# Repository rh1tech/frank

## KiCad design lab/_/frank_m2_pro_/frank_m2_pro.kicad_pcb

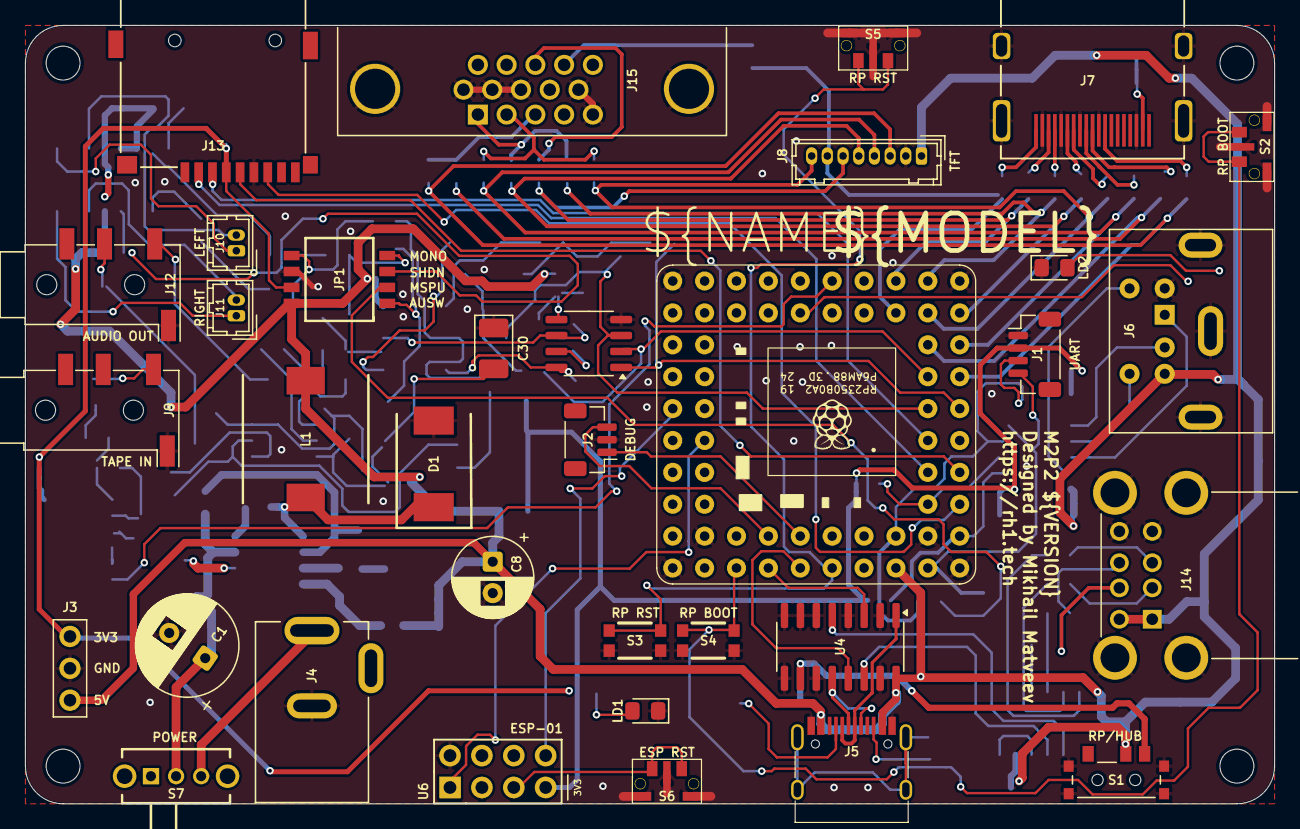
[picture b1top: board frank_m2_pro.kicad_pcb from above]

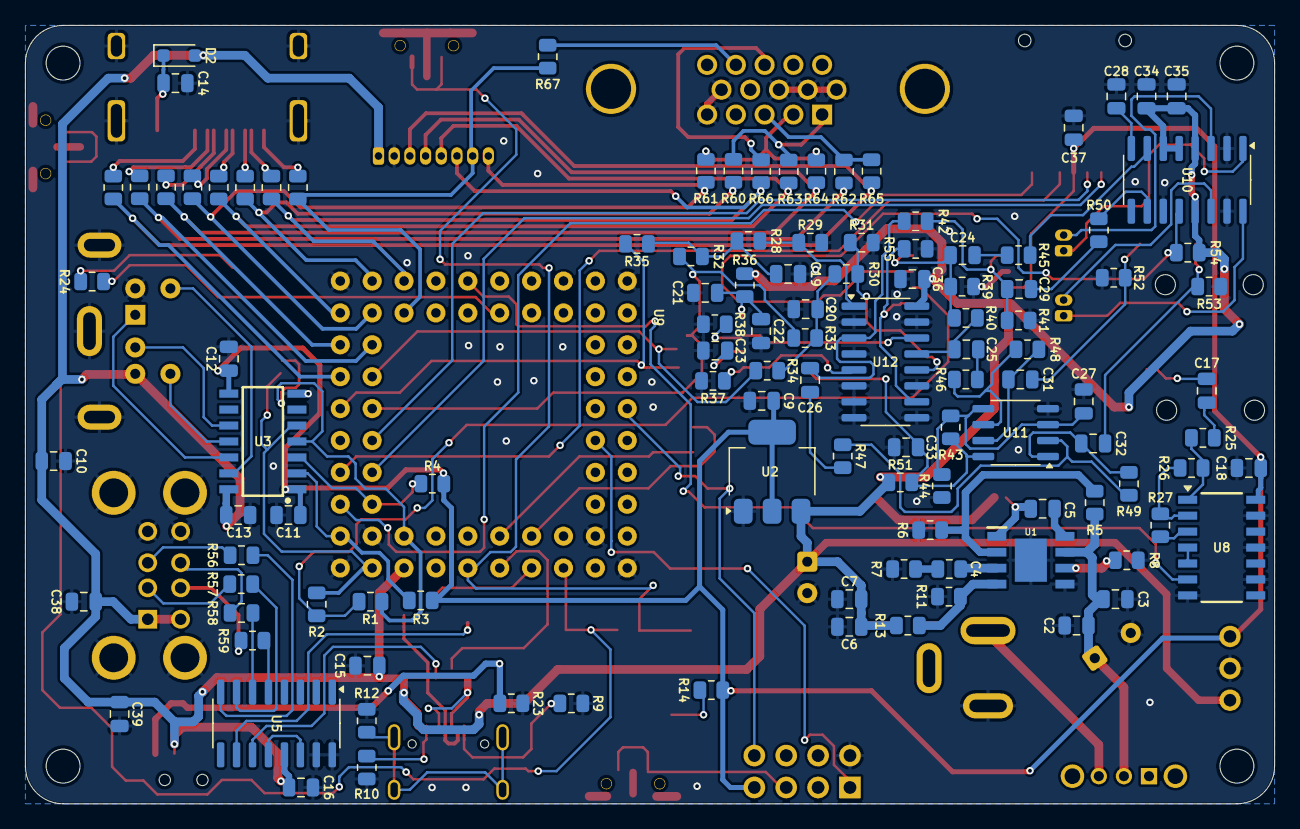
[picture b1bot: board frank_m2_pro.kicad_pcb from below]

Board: 2 copper layers, 99.5 x 62.0 mm, 150 parts (112 on the bottom side), 119 nets.

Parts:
C1: 680u; Capacitor (Radial_D8.0mm_P3.50mm)
C2, C7, C9, C21, C23, C25, C26, C27, C31, C32, C38, C39: 10u; C_0805_2012Metric
C3, C5, C6, C10, C11, C12, C13, C14, C15, C17, C18, C22, C28, C33, C36, C37: 100n; C_0805_2012Metric
C4: 150pF; R_0805_2012Metric
C8: 220u; Capacitor (Radial_D6.3mm_P2.50mm)
C16: 4.7u; C_0805_2012Metric
C19, C20: 47n; C_0805_2012Metric
C24, C29, C34: 1u; C_0805_2012Metric
C30: 10u; Capacitor (3528, tantalum, polar)
C35: 47u; C_0805_2012Metric
D1: 1N5822; SS34
D2: 1N5819WS; Diode (SOD-323)
H1, H2, H3, H4: Hole 2.7mm; Mounting Hole (2.7mm)
J1: UART; JST_SH_BM04B-SRSS-TB_1x04-1MP_P1.00mm_Vertical
J2: DEBUG; JST_SH_BM03B-SRSS-TB_1x03-1MP_P1.00mm_Vertical
J3: PWR; Pin Header (1x03)
J4: DC-005-5A-2.0; XKB_DC-005-5A-2.0
J5: USB4215-03-A; USB Type C
J6: MDC-036; MiniDIN (6 Pin, female)
J7: DC3RX19JA2; HDMI (female)
J8: Pin Header 1x08; Connector Female 1.25 JST 8P
J9, J12: PJ-320D; Jack (3.5mm, PJ-320D)
J10: PAM L; Connector Female 1.25 JST 2P
J11: PAM R; Connector Female 1.25 JST 2P
J13: 104031-0811; MicroSD (SMD, long)
J14: SS-52100-004; USB Type A (stacked)
J15: VGA; D-SUB (15 pin, female)
JP1: Config Switches; CHS04TB1
L1: 22uH; CDRH104RNP
LD1: Green; LED (0805)
LD2: Blue; LED (0805)
R1, R2, R3, R4, R23, R28, R30, R40, R42, R43, R44, R45, R46, R47, R50, R54, R55: 10K; R_0805_2012Metric
R5, R7, R8, R26, R27: 100K; R_0805_2012Metric
R6: 24K; R_0805_2012Metric
R9, R10: 5.1K; R_0805_2012Metric
R11: 8.2K; R_0805_2012Metric
R12: 1M; R_0805_2012Metric
R13: 43K; R_0805_2012Metric
R14, R24, R34, R35, R63, R64, R65: 1K; R_0805_2012Metric
R15, R16, R17, R18, R19, R20, R21, R22: 270R; R_0805_2012Metric
R25: 4.7K; R_0805_2012Metric
R29, R31, R32, R33, R39, R41: 2K; R_0805_2012Metric
R36, R51, R66, R67: 100R; R_0805_2012Metric
R37, R38: 470R; R_0805_2012Metric
R48, R49: 47K; R_0805_2012Metric
R52, R53: 20K; R_0805_2012Metric
R56, R57, R58, R59: 22R; R_0805_2012Metric
R60, R61, R62: 330R; R_0805_2012Metric
S1: MSK12C02; SW_MSK12C02
S2: RP BOOT; TS-1234VW
S3: RP Reset; KMR_2
S4: RP BOOT; KMR_2
S5: RP Reset; TS-1234VW
S6: ESP Reset; TS-1234VW
S7: SK12D07VG3NS
U1: MP1584EN-LF-Z; SOIC127P600X170-9N
U2: AMS1117 3.3; SOT-223
U3: TXS0104EDR; SOIC127P600X175-14N
U4, U12: 74HC4052D; SOP-16
U5: MW7211A; SOP-16
U6: ESP-01v090; ESP-01
U7: Pimoroni PGA2350; PGA2350
U8: CD4069UBM; SOIC127P600X175-14N
U9: TDA1387T; SO-8
U10: PAM8403D; SOP-16
U11: LM358; SO-8

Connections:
+3V3: C9.1, C11.1, C12.1, C18.1, C37.2, J1.2, J3.1, J13.4 (VDD), JP1.7, R3.2, R4.2, R14.2, U2.2 (VO), U3.1 (VCCA), U3.8 (OE), U6.7 (VCC), U8.14 (VDD)
/AMP_L: C25.1, R40.1, U12.13 (1Z)
/AMP_OUT_L: C31.2, J12.T, R52.2
/AMP_OUT_R: C32.2, J12.R, R53.2
/AMP_R: C26.1, R42.1, U12.3 (2Z)
/AUDIOSW: JP1.1, R55.2, U12.10 (S0)
/Audio/AMP_PAM_OUTL_M: J10.2, U10.3 (-OUTL)
/Audio/AMP_PAM_OUTL_P: J10.1, U10.1 (+OUT_L)
/Audio/AMP_PAM_OUTR_M: J11.2, U10.14 (-OUT_R)
/Audio/AMP_PAM_OUTR_P: J11.1, U10.16 (+OUT_R)
/BOOTSEL: S2.1, S4.1, S4.3, U7.51 (BOOTSEL)
/ERST: S6.1, U6.5 (RST)
/HDM: U4.5 (2Y1), U5.10 (DMU)
/HDP: U4.14 (1Y1), U5.11 (DPU)
/MONO_L: C24.1, JP1.4, R39.1, R40.2
/MONO_R: C29.1, JP1.5, R41.1, R42.2
/MSPUP3V3: JP1.2, R1.2, R2.2
/PDM: U4.3 (2Z), U7.53 (USB_DM)
/PDP: U4.13 (1Z), U7.54 (USB_DP)
/PGPIO0: J1.3, R1.1, U3.4 (A3), U7.61 (GP0)
/PGPIO1: J1.4, R2.1, U3.5 (A4), U7.62 (GP1)
/PGPIO2: R3.1, U3.2 (A1), U7.2 (GP2)
/PGPIO3: R4.1, U3.3 (A2), U7.3 (GP3)
/PGPIO4: J13.7 (DAT0), U7.4 (GP4)
/PGPIO5: J13.2 (DAT3/CD), U7.5 (GP5)
/PGPIO6: J13.5 (CLK), U7.6 (GP6)
/PGPIO7: J13.3 (CMD), U7.7 (GP7)
/PGPIO9: R32.1, R33.1, U7.9 (GP9), U9.3 (DATA)
/PGPIO10: R35.2, U7.10 (GP10), U9.1 (SCLK)
/PGPIO11: R34.2, U7.11 (GP11), U9.2 (LRCK)
/PGPIO12: J8.3, R17.2, R65.1, U7.12 (GP12)
/PGPIO13: R21.2, R62.1, U7.13 (GP13)
/PGPIO14: J8.4, R15.2, R64.1, U7.14 (GP14)
/PGPIO15: J8.8, R18.2, R61.1, U7.15 (GP15)
/PGPIO16: J8.5, R19.2, R63.1, U7.16 (GP16)
/PGPIO17: R22.2, R60.1, U7.17 (GP17)
/PGPIO18: J8.6, R16.2, R66.2, U7.19 (GP18)
/PGPIO19: J8.7, R20.2, R67.2, U7.20 (GP19)
/PGPIO22: U7.23 (GP22), U8.6 (I=*C)
/PGPIO38: U6.8 (URXD), U7.40 (GP38)
/PGPIO39: U6.1 (UTXD), U7.41 (GP39)
/PRUN: S3.1, S3.3, S5.1, U7.56 (RUN)
/PS2/KB_CLK_5V: J6.5, U3.13 (B1)
/PS2/KB_DATA_5V: J6.1, U3.12 (B2)
/PS2/MS_CLK_5V: J6.6, U3.11 (B3)
/PS2/MS_DATA_5V: J6.2, U3.10 (B4)
/PSWCLK: J2.1, U7.55 (SWCLK)
/PSWDIO: J2.3, U7.52 (SWDIO)
/PWM_L: R30.2, R31.1, U12.12 (1Y0)
/PWM_R: R28.2, R29.1, U12.1 (2Y0)
/Power/VBUS_IN: C1.1, C2.1, C3.1, R5.2, S7.2, U1.7 (VIN)
/SD1M: R57.1, U5.7 (DM3)
/SD1P: R56.1, U5.8 (DP3)
/SD2M: R59.1, U5.5 (DM2)
/SD2P: R58.1, U5.6 (DP2)
/SHND: JP1.3, R54.2, U10.12 (SHND)
/TDA_L: R38.2, U9.6 (A_LEFT), U12.14 (1Y1)
/TDA_R: R37.1, U9.8 (A_RIGHT), U12.5 (2Y1)
/Tape In/TAPE: C17.2, J9.T
/UDM: J5.5 (DN2), J5.7 (DN1), U4.1 (2Y0)
/UDP: J5.6 (DP1), J5.8 (DP2), U4.12 (1Y0)
/USBSW: R23.2, S1.3, U4.10 (S0)
GND: C1.2, C2.2, C3.2, C6.1, C7.2, C8.2, C9.2, C10.2, C11.2, C12.2, C13.2, C14.2, C15.1, C16.2, C18.2, C19.2, C20.2, C21.2, C22.2, C23.2, C27.1, C28.2, C30.1, C33.1, C34.2, C35.2, C36.1, C37.1, C38.2, C39.2, D1.2 (A), J1.1, J2.2, J3.2, J4.2, J5.1 (GND), J5.12 (GND), J6.3, J7.2 (G_D2), J7.5 (G_D1), J7.8 (G_D0), J7.11 (G_CLK), J7.17 (G_DDC/CEC), J7.20 (SHIELD1), J7.21 (SHIELD2), J7.22 (SHIELD3), J7.23 (SHIELD4), J8.2, J9.S, J12.S, J13.6 (VSS), J14.4 (GND1), J14.8 (GND2), J14.9 (Shield), J15.0, J15.5, J15.6, J15.7, J15.8, J15.10, JP1.6, LD1.1 (K), LD2.1 (K), R6.2, R7.2, R8.2, R9.1, R10.1, R11.1, R12.1, R23.1, R29.2, R31.2, R37.2, R38.1, R39.2, R41.2, R44.1, R52.1, R53.1, R55.1, S1.4_1 (GND), S1.4_2 (GND), S1.4_3 (GND), S1.4_4 (GND), S2.2, S2.3 (GND), S3.2, S3.4, S4.2, S4.4, S5.2, S5.3 (GND), S6.2, S6.3 (GND), U1.5 (GND), U1.9 (EP), U2.1 (GND), U3.7 (GND), U4.2 (2Y2), U4.4 (2Y3), U4.6 (~E), U4.7 (VEE), U4.8 (GND), U4.9 (S1), U4.11 (1Y3), U4.15 (1Y2), U5.15 (GND), U5.16 (GND), U6.2 (GND), U7.1 (GND), U7.18 (GND), U7.33 (GND), U7.48 (GND), U8.7 (VSS), U8.9 (D14), U8.11 (E), U8.13 (F), U9.4 (AGND), U10.2 (PGND), U10.11 (GND), U10.15 (PGND), U11.4 (V-), U12.2 (2Y2), U12.4 (2Y3), U12.6 (~E), U12.7 (VEE), U12.8 (GND), U12.9 (S1), U12.11 (1Y3), U12.15 (1Y2)
GP25: R24.2, U7.26 (GP25)
unnamed: C4.2, R7.1
unnamed: C17.1, R25.2
unnamed: C19.1, R28.1, R32.2, R35.1
unnamed: C20.1, R30.1, R33.2, R34.1
unnamed: C24.2, R45.2
unnamed: C25.2, R46.2
unnamed: C26.2, R47.2
unnamed: C29.2, R50.2
unnamed: C31.1, R48.1, U11.7
unnamed: C32.1, R49.1, U11.1
unnamed: C5.2, D1.1 (K), L1.1, U1.1 (SW)
unnamed: C14.1, D2.1 (K), J7.18 (+5V)
unnamed: J4.1, S7.3
unnamed: J5.4 (CC1), R9.2
unnamed: J5.10 (CC2), R10.2
unnamed: J5.13 (SHIELD), R12.2
unnamed: J7.12 (CLKN), R17.1
unnamed: J7.10 (CLKP), R21.1
unnamed: J7.9 (D0N), R15.1
unnamed: J7.7 (D0P), R18.1
unnamed: J7.6 (D1N), R19.1
unnamed: J7.4 (D1P), R22.1
unnamed: J7.3 (D2N), R16.1
unnamed: J7.1 (D2P), R20.1
unnamed: J14.3 (D1+), R56.2
unnamed: J14.2 (D1-), R57.2
unnamed: J14.7 (D2+), R58.2
unnamed: J14.6 (D2-), R59.2
unnamed: J15.1, R60.2, R63.2
unnamed: J15.2, R61.2, R64.2
unnamed: J15.3, R62.2, R65.2
unnamed: J15.13, R66.1
unnamed: J15.14, R67.1
unnamed: LD1.2 (A), R14.1
unnamed: LD2.2 (A), R24.1
unnamed: C5.1, U1.8 (BST)
unnamed: C4.1, U1.3 (COMP)
unnamed: R5.1, R6.1, U1.2 (EN)
unnamed: R11.2, R13.2, U1.4 (FB)
unnamed: R8.1, U1.6 (FREQ)
unnamed: U5.12 (VD33), U5.14 (VD3)
unnamed: R25.1, R26.2, U8.1 (A)
unnamed: R27.1, U8.3 (B)
unnamed: U8.4 (H=*B), U8.5 (C)
unnamed: R26.1, R27.2, U8.2 (G-*A)
unnamed: C23.1, U9.7 (FLT)
unnamed: C21.1, C22.1, R36.1, U9.5 (VA)
unnamed: R45.1, U10.7 (INL)
unnamed: R50.1, U10.10 (INR)
unnamed: C28.1, U10.8 (VREF)
unnamed: C27.2, R43.1, R44.2, U11.3 (+), U11.5 (+)
unnamed: R47.1, R49.2, U11.2 (-)
unnamed: R46.1, R48.2, U11.6 (-)
unnamed: C30.2, C33.2, R43.2, R51.2, U11.8 (V+)
VBUS: C6.2, C7.1, C8.1, C10.1, C13.1, C15.2, C16.1, C34.1, C35.1, C36.2, C38.1, C39.1, D2.2 (A), J3.3, J5.2 (VBUS), J5.11 (VBUS), J6.4, J8.1, J14.1 (VBUS1), J14.5 (VBUS2), JP1.8, L1.2, R13.1, R36.2, R51.1, R54.1, S1.2, U2.3 (VI), U3.14 (VCCB), U4.16 (VCC), U5.13 (VDD5), U7.60 (VBUS), U10.4 (PVDD), U10.5 (MUTE), U10.6 (VDD), U10.13 (PVDD), U12.16 (VCC)

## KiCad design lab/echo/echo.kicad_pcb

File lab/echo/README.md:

# Protea

Protea is an open-source, feature-rich serial terminal and Wi-Fi modem PCB, designed in KiCad and released under the GNU General Public License (version 3 or later). Inspired by David Hansel's](https://github.com/dhansel) [VersaTerm](https://github.com/dhansel/VersaTerm) and [Richard Bettridge's](https://richardbettridge.com/) [RS232 Serial Wi-Fi Modem](https://github.com/TheOldNet/vintage-computer-wifi-modem), Protea combines modern connectivity with classic terminal functionality.

## Key Features

* **Plug-and-Play Operation**: simply connect a standard USB keyboard and an HDMI display—no additional host system or software required. Protea powers on instantly, requiring no boot-up sequence or shutdown procedure.
* **Universal Serial I/O**. Supports both RS232 and TTL (3.3 V or 5 V) serial levels. Choose from fixed presets or any custom baud rate between 50 and 921 600 baud. Full hardware (RTS/CTS) and software (XOn/XOff) flow control ensure reliable data transfer.
* **Comprehensive VT100 Emulation**. Full support for VT100 attributes—including bold, underline, blink, inverse, double width, and double height—and 16 ANSI colors. Advanced control-sequence compatibility passes VTTest for VT52/VT100/VT102 conformance.
* **PETSCII Mode**. Emulates the PETSCII character set and control codes used by the Commodore 64, complete with an authentic PETSCII bitmap font.
* **RP2040-Powered**. Built around the Raspberry Pi RP2040 microcontroller, Protea delivers instant-on performance and robust processing for terminal emulation.
* **Built-In Wi-Fi Modem**. Integrates an ESP8266EX module with on-board antenna, providing transparent serial-to-Wi-Fi bridging for telnet, web-based interfaces, or custom network protocols. Enables remote terminal sessions over local networks or the Internet.
* **Highly Configurable**. Customizable color palettes, and savable configuration profiles mean you can tailor Protea to any workflow. A built-in menu system allows on-the-fly adjustments without recompiling firmware.

Protea brings together the convenience of modern hardware with the nostalgia and versatility of vintage terminal interfaces—ideal for hobbyists, retro-computing enthusiasts, and embedded systems developers.

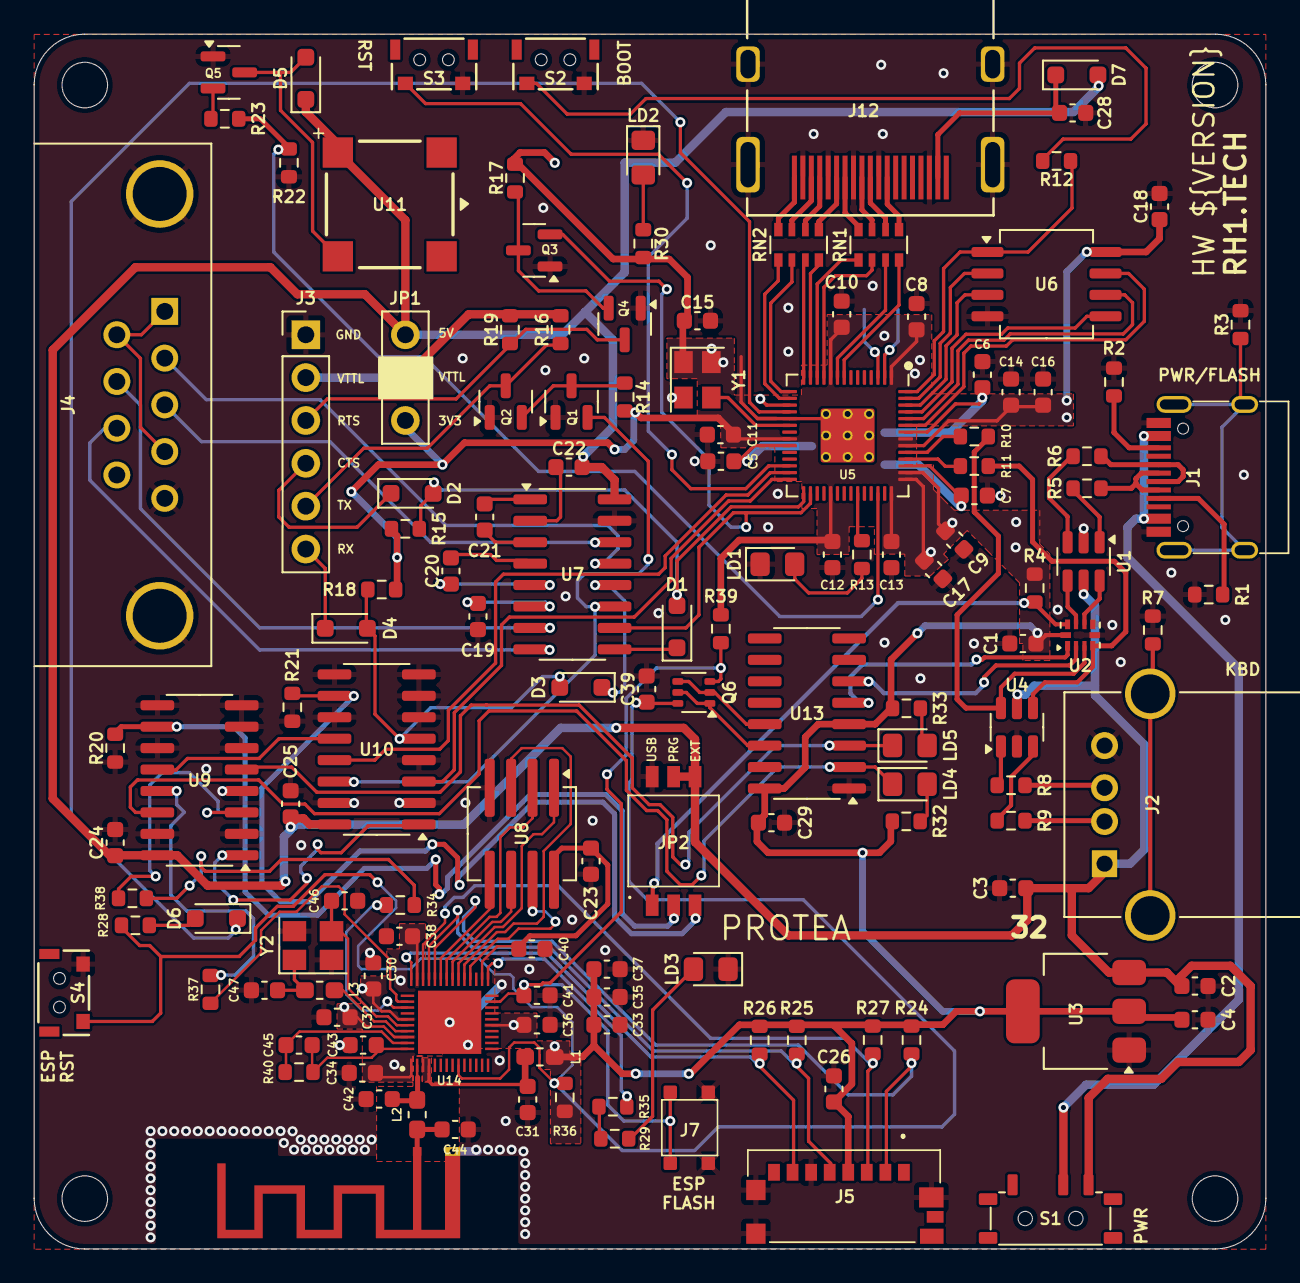
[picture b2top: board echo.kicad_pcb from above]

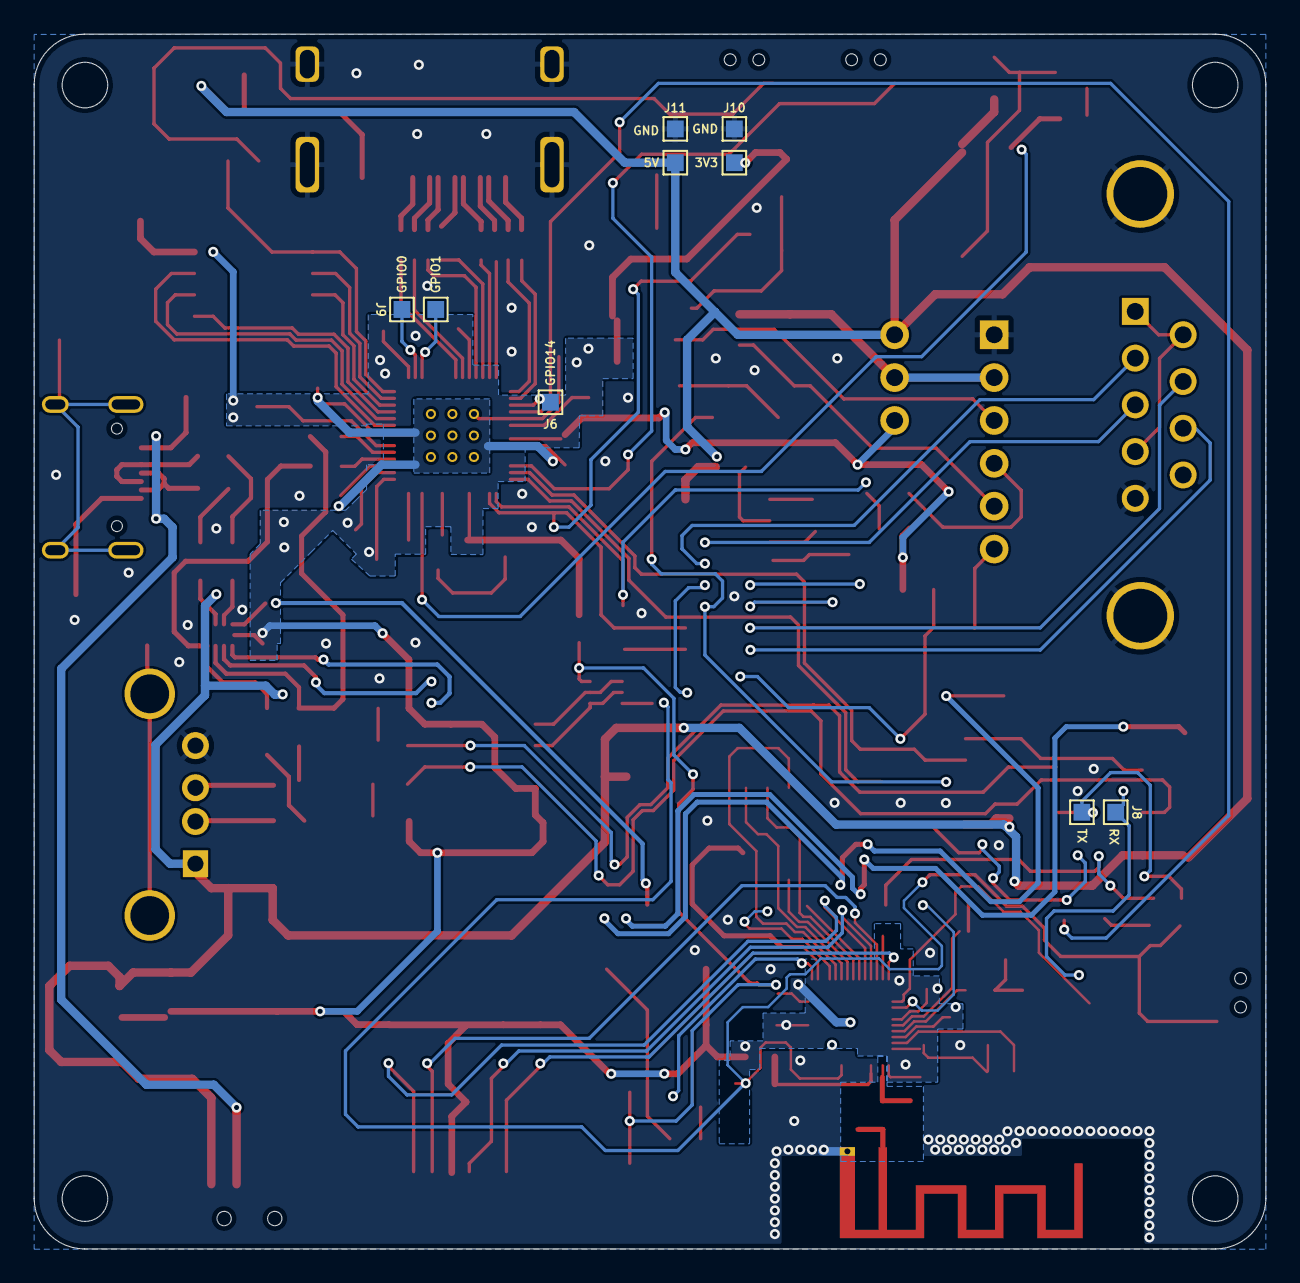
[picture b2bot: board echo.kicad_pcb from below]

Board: 2 copper layers, 73.0 x 72.0 mm, 146 parts (5 on the bottom side), 128 nets.

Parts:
AE1: Antenna_Shield; Antenna (2.4GHz)
C1, C5, C6, C8, C10, C11, C12, C13, C14, C15, C16, C17, C18, C23, C24, C25, C26, C28, C29, C31, C33, C34, C36, C38: 100n; Capacitor (0603, S)
C2, C3, C4, C35: 10u; Capacitor (0603, S)
C7, C9, C19, C20, C21, C22, C30, C37, C40: 1u; Capacitor (0603, S)
C32: 100p; Capacitor (0603, S)
C39, C41: 1n; Capacitor (0603, S)
C42: 1.5pF; Capacitor (0603, S)
C43: 10n; Capacitor (0603, S)
C44: 2.4pF; Capacitor (0603, S)
C45: 3.3n; Capacitor (0603, S)
C46, C47: 12p; Capacitor (0603, S)
D1, D2, D3, D4, D5, D6: 1N4148; Diode (SOD-323)
D7: 1N5819WS; Diode (SOD-323)
H1, H2, H3, H4: MountingHole; Mounting Hole (2.7mm)
J1: USB4215-03-A; USB Type C
J2: 676430910; USB Type A (single)
J3: TTL; PinHeader_1x06_P2.54mm_Vertical
J4: D-SUB 9 Male; D-SUB (9 pin, male, top mount)
J5: 0475710001; MicroSD (SMD, short)
J6: Defaults; Test Point (1mm x 1)
J7: Flash; Button (SMD, 3x3mm, 1-1)
J8, J9, J10, J11: Test Points (1mm x 2)
J12: DC3RX19JA2; HDMI (female)
JP1: TTL PWR; PinHeader_1x03_P2.54mm_Vertical
JP2: Main Jumpers; DS05127203BKSMTTR
L1: 2nH; Inductor (0603 1.05x0.95)
L2: 2.7nH/0R; Inductor (0603 1.05x0.95)
L3: 24nH/0R; Inductor (0603 1.05x0.95)
LD1, LD3: Blue; LED (0805)
LD2: Green; LED (0805)
LD4, LD5: Orange; LED (0805)
Q1, Q2, Q3, Q4, Q5: 2N7000; SOT-23
Q6: UMH3N; SOT-363
R1, R2: 5.1K; Resistor (0603, S)
R3, R7: 1M; Resistor (0603, S)
R4, R20, R21, R22, R24, R25, R26, R27, R36, R39: 10K; Resistor (0603, S)
R5, R6, R8, R9: 22R; Resistor (0603, S)
R10, R11: 27R; Resistor (0603, S)
R12, R13, R14, R15, R17, R18, R30: 1K; Resistor (0603, S)
R16, R19, R29: 470R; Resistor (0603, S)
R23: 100R; Resistor (0603, S)
R28: 200R; Resistor (0603, S)
R32, R33: 1.5K; Resistor (0603, S)
R34: 499R; Resistor (0603, S)
R35: 0R; Resistor (0603, S)
R37, R38: 330R; Resistor (0603, S)
R40: 20K; Resistor (0603, S)
RN1, RN2: 270R; Resistor Array (4x0603)
S1: Power Switch; Switch (MSK12C02)
S2: Boot; TACT-SIDE-4623
S3: Reset; TACT-SIDE-4623
S4: ESP RST; TACT-SIDE-4623
U1, U4: USBLC6-2SC6; SOT-23-6
U2: TS3USB221RSER; UQFN-10
U3: NCP1117 3.3; SOT-223
U5: RP2040; QFN 56
U6: W25Q16JVSSIQ; SOIC-8
U7: MAX232CSE+; SOP-16
U8: W25Q32JVSIQ; SOIC-8 (Longer)
U9, U10: 74HC4052D; SOP-16
U11: CMT-7525-80-SMT-TR; CMT752580SMTTR
U13: CH340C; SOP-16
U14: ESP32-D0WD-V3; QFN35P500X500X90-49N-D
Y1: ASE-12MHz; Crystal (3225, active)
Y2: 40MHz; Crystal (3225)

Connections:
+3.3VP: C31.1, L1.2, U14.3 (VDD3P3_1), U14.4 (VDD3P3_2)
+3V3: C1.2, C4.1, C8.1, C9.1, C10.1, C11.1, C12.1, C13.1, C14.1, C15.1, C16.1, C17.1, C18.1, C26.2, C29.1, C30.1, C32.1, C33.1, C34.1, C35.1, C36.1, C37.1, C38.1, J5.P4 (VDD), J10.2, JP1.3, L1.1, R4.1, R14.2, R15.2, R17.2, R18.2, R24.2, R25.2, R26.2, R27.2, R30.2, R32.2, R33.1, R36.2, R39.2, U2.10 (VCC), U3.2 (VO), U5.1 (IOVDD), U5.10 (IOVDD), U5.22 (IOVDD), U5.33 (IOVDD), U5.42 (IOVDD), U5.43 (ADC_AVDD), U5.44 (VREG_IN), U5.48 (USB_VDD), U5.49 (IOVDD), U6.8 (VCC), U13.4 (3V), U13.16 (VCC), U14.1 (VDDA_1), U14.19 (VDD3P3_RTC), U14.37 (VDD3P3_CPU), U14.43 (VDDA_2), U14.46 (VDDA_3), Y1.1 (EN), Y1.4 (Vdd)
/ESP32/ANT: AE1.1 (A), C44.1, L2.1
/ESP32/CAP1: C43.1, C45.1, R40.2, U14.48 (CAP1)
/ESP32/CAP2: C45.2, R40.1, U14.47 (CAP2)
/ESP32/LNA_IN: C42.1, L2.2, U14.2 (LNA_IN)
/ESP32/XTAL_N: C46.1, U14.44 (XTAL_N), Y2.3
/ESP32/XTAL_P: L3.1, U14.45 (XTAL_P)
/ESP_CHIP_PU: C39.1, Q6.6 (C1), R28.1, R36.1, S4.1, U14.9 (CHIP_PU)
/ESP_DTR: Q6.2 (B1), Q6.4 (E2), U13.13 (DTR)
/ESP_GPIO0: C41.1, J7.2, Q6.3 (C2), R39.1, U14.23 (GPIO0)
/ESP_GPIO5: J5.P2 (CD/DAT3), R24.1, U14.34 (GPIO5)
/ESP_GPIO16: R29.1, R35.2
/ESP_GPIO18: J5.P5 (CLK), R25.1, U14.35 (GPIO18)
/ESP_GPIO19: J5.P7 (DAT0), R26.1, U14.38 (GPIO19)
/ESP_GPIO23: J5.P3 (CMD), R27.1, U14.36 (GPIO23)
/ESP_RTS: Q6.1 (E1), Q6.5 (B2), U13.14 (RTS)
/ESP_RXD: J8.1, R37.1, U9.13 (1Z)
/ESP_SCK/CLK: U8.6 (CLK), U14.31 (SD_CLK)
/ESP_SCS/CMD: U8.1 (~CS), U14.30 (SD_CMD)
/ESP_SDI/SD1: U8.5 (DI(IO0)), U14.33 (SD_DATA_1)
/ESP_SDO/SD0: U8.2 (DO(IO1)), U14.32 (SD_DATA_0)
/ESP_SHD/SD2: U8.7 (IO3), U14.28 (SD_DATA_2)
/ESP_SWP/SD3: U8.3 (IO2), U14.29 (SD_DATA_3)
/ESP_TXD: J8.2, R38.1, U9.3 (2Z)
/ESP_U0RXD: R37.2, U14.40 (U0RXD)
/ESP_U0TXD: R34.2, R38.2
/M1_SW: JP2.2, R20.2, U9.10 (S0)
/M2_SW: JP2.3, R21.2, U10.10 (S0)
/Multiplexers/MP_RX: U9.12 (1Y0), U10.12 (1Y0)
/Multiplexers/MP_TX: U9.1 (2Y0), U10.1 (2Y0)
/Power/UC_D+: U1.4 (I/O2), U2.8 (D+)
/Power/UC_D-: U1.6 (I/O1), U2.7 (D-)
/RP2040/GPIO25: R13.2, U5.37 (GPIO25)
/RP2040/QSPI_SCLK: U5.52 (QSPI_SCLK), U6.6 (CLK)
/RP2040/QSPI_SD0: U5.53 (QSPI_SD0), U6.5 (DI(IO0))
/RP2040/QSPI_SD1: U5.55 (QSPI_SD1), U6.2 (DO(IO1))
/RP2040/QSPI_SD2: U5.54 (QSPI_SD2), U6.3 (IO2)
/RP2040/QSPI_SD3: U5.51 (QSPI_SD3), U6.7 (IO3)
/RP2040/QSPI_SS: R12.1, U5.56 (QSPI_SS), U6.1 (~CS)
/RP2040/XIN: U5.20 (XIN), Y1.3 (OUT)
/RP_D+: R10.1, U2.3 (2D+), U4.6 (I/O1)
/RP_D-: R11.1, U2.4 (2D-), U4.4 (I/O2)
/RP_GPIO0: J9.1, U5.2 (GPIO0)
/RP_GPIO1: J9.2, U5.3 (GPIO1)
/RP_GPIO6: RN1.4 (R4.1), U5.8 (GPIO6)
/RP_GPIO7: RN1.3 (R3.1), U5.9 (GPIO7)
/RP_GPIO8: RN1.2 (R2.1), U5.11 (GPIO8)
/RP_GPIO9: RN1.1 (R1.1), U5.12 (GPIO9)
/RP_GPIO10: RN2.4 (R4.1), U5.13 (GPIO10)
/RP_GPIO11: RN2.3 (R3.1), U5.14 (GPIO11)
/RP_GPIO12: RN2.2 (R2.1), U5.15 (GPIO12)
/RP_GPIO13: RN2.1 (R1.1), U5.16 (GPIO13)
/RP_GPIO14: J6.1, U5.17 (GPIO14)
/RP_GPIO15: D6.1 (K), U5.18 (GPIO15)
/RP_GPIO16: U5.27 (GPIO16), U10.13 (1Z)
/RP_GPIO17: U5.28 (GPIO17), U10.3 (2Z)
/RP_GPIO18: D1.2 (A), D2.2 (A), R15.1, U5.29 (GPIO18)
/RP_GPIO19: Q3.2 (G), U5.30 (GPIO19), U7.10 (T2IN)
/RP_GPIO28: R22.2, R23.2, U5.40 (GPIO28_ADC2)
/RP_RUN: S3.1, U5.26 (RUN)
/RS232, TTL/C1+: C21.2, U7.1 (C1+)
/RS232, TTL/C1-: C21.1, U7.3 (C1-)
/RS232, TTL/C2+: C20.2, U7.4 (C2+)
/RS232, TTL/C2-: C20.1, U7.5 (C2-)
/RS232, TTL/CTS_IN: J4.7, U7.7 (T2OUT)
/RS232, TTL/CTS_MAX: D1.1 (K), U7.9 (R2OUT)
/RS232, TTL/CTS_TTL: D2.1 (K), J3.4
/RS232, TTL/RTS_IN: J4.8, U7.8 (R2IN)
/RS232, TTL/RTS_TTL: J3.3, Q4.3 (D), R19.1
/RS232, TTL/RX_IN: J4.3, U7.14 (T1OUT)
/RS232, TTL/RX_MAX: D3.1 (K), U7.12 (R1OUT)
/RS232, TTL/RX_TTL: D4.1 (K), J3.6
/RS232, TTL/TX_IN: J4.2, U7.13 (R1IN)
/RS232, TTL/TX_TTL: J3.5, Q2.3 (D), R16.1
/RS232, TTL/V+: C22.1, U7.2 (V+)
/RS232, TTL/V-: C19.1, U7.6 (V-)
/RS232, TTL/VTTL: J3.2, JP1.2, R16.2, R19.2
/RS232_RX: D3.2 (A), D4.2 (A), R18.1, U10.5 (2Y1)
/RS232_TX: Q1.2 (G), U7.11 (T1IN), U10.14 (1Y1)
/UMP_SW: JP2.1, R4.2, U2.9 (S)
/UT_D+: U2.1 (1D+), U13.5 (D+)
/UT_D-: U2.2 (1D-), U13.6 (D-)
/UT_RX: LD5.1 (K), U9.5 (2Y1), U13.3 (RxD)
/UT_TX: LD4.1 (K), U9.14 (1Y1), U13.2 (TxD)
/VDD_SDIO: C23.1, C40.1, U8.8 (VCC), U14.26 (VDD_SDIO)
GND: AE1.2 (Shield), C1.1, C2.2, C3.2, C4.2, C5.2, C6.2, C7.2, C8.2, C9.2, C10.2, C11.2, C12.2, C13.2, C14.2, C15.2, C16.2, C17.2, C18.2, C19.2, C23.2, C24.1, C25.1, C26.1, C28.2, C29.2, C30.2, C31.2, C32.2, C33.2, C34.2, C35.2, C36.2, C37.2, C38.2, C39.2, C40.2, C41.2, C42.2, C43.2, C44.2, C46.2, C47.2, J1.1 (GND), J1.12 (GND), J2.4 (GND), J3.1, J4.5, J5.G1 (GND_1), J5.G2 (GND_2), J5.G3 (GND_3), J5.P6 (VSS), J7.1, J10.1, J11.1, J12.2 (G_D2), J12.5 (G_D1), J12.8 (G_D0), J12.11 (G_CLK), J12.17 (G_DDC/CEC), J12.20 (SHIELD1), J12.21 (SHIELD2), J12.22 (SHIELD3), J12.23 (SHIELD4), JP2.6, LD1.1 (K), LD2.1 (K), LD3.1 (K), Q1.1 (S), Q2.1 (S), Q3.1 (S), Q4.1 (S), Q5.1 (S), R1.1, R2.1, R3.2, R7.2, R20.1, R21.1, R22.1, S2.2, S3.2, S4.2, U1.2 (GND), U2.5 (GND), U2.6 (~OE), U3.1 (GND), U4.2 (GND), U5.19 (TESTEN), U5.57 (GND), U6.4 (GND), U7.15 (GND), U8.4 (GND), U9.2 (2Y2), U9.4 (2Y3), U9.6 (~E), U9.7 (VEE), U9.8 (GND), U9.9 (S1), U9.11 (1Y3), U9.15 (1Y2), U10.2 (2Y2), U10.4 (2Y3), U10.6 (~E), U10.7 (VEE), U10.8 (GND), U10.9 (S1), U10.11 (1Y3), U10.15 (1Y2), U13.1 (GND), U14.49 (GND), Y1.2 (GND), Y2.2, Y2.4
unnamed: C47.1, L3.2, Y2.1
unnamed: D5.2 (A), Q5.3 (D), U11.2 (-)
unnamed: D6.2 (A), R28.2
unnamed: C28.1, D7.1 (K), J12.18 (+5V)
unnamed: J1.4 (CC1), R1.2
unnamed: J1.10 (CC2), R2.2
unnamed: J1.5 (DN2), J1.7 (DN1), R5.2
unnamed: J1.6 (DP1), J1.8 (DP2), R6.2
unnamed: J1.13 (SHIELD), R3.1
unnamed: J2.3 (D+), R8.2
unnamed: J2.2 (D-), R9.2
unnamed: J2.5 (Shield), R7.1
unnamed: J4.1, J4.4, J4.6
unnamed: J12.12 (CLKN), RN1.5 (R4.2)
unnamed: J12.10 (CLKP), RN1.6 (R3.2)
unnamed: J12.9 (D0N), RN1.7 (R2.2)
unnamed: J12.7 (D0P), RN1.8 (R1.2)
unnamed: J12.6 (D1N), RN2.5 (R4.2)
unnamed: J12.4 (D1P), RN2.6 (R3.2)
unnamed: J12.3 (D2N), RN2.7 (R2.2)
unnamed: J12.1 (D2P), RN2.8 (R1.2)
unnamed: LD1.2 (A), R13.1
unnamed: LD2.2 (A), R30.1
unnamed: LD3.2 (A), R29.2
unnamed: LD4.2 (A), R32.1
unnamed: LD5.2 (A), R33.2
unnamed: Q1.3 (D), Q2.2 (G), R14.1
unnamed: Q3.3 (D), Q4.2 (G), R17.1
unnamed: Q5.2 (G), R23.1
unnamed: R5.1, U1.1 (I/O1)
unnamed: R6.1, U1.3 (I/O2)
unnamed: R8.1, U4.1 (I/O1)
unnamed: R9.1, U4.3 (I/O2)
unnamed: R12.2, S2.1
unnamed: J1.2 (VBUS), J1.11 (VBUS), S1.2 (B)
unnamed: R11.2, U5.46 (USB_DM)
unnamed: R10.2, U5.47 (USB_DP)
unnamed: C5.1, C6.1, C7.1, U5.23 (DVDD), U5.45 (VREG_VOUT), U5.50 (DVDD)
unnamed: R35.1, U14.25 (GPIO16)
unnamed: R34.1, U14.41 (U0TXD)
VBUS: C2.1, C3.1, C22.2, C24.2, C25.2, D5.1 (K), D7.2 (A), J2.1 (VBUS), J11.2, JP1.1, JP2.4, JP2.5, S1.3 (A), U1.5 (VBUS), U3.3 (VI), U4.5 (VBUS), U7.16 (VCC), U9.16 (VCC), U10.16 (VCC), U11.1 (+)

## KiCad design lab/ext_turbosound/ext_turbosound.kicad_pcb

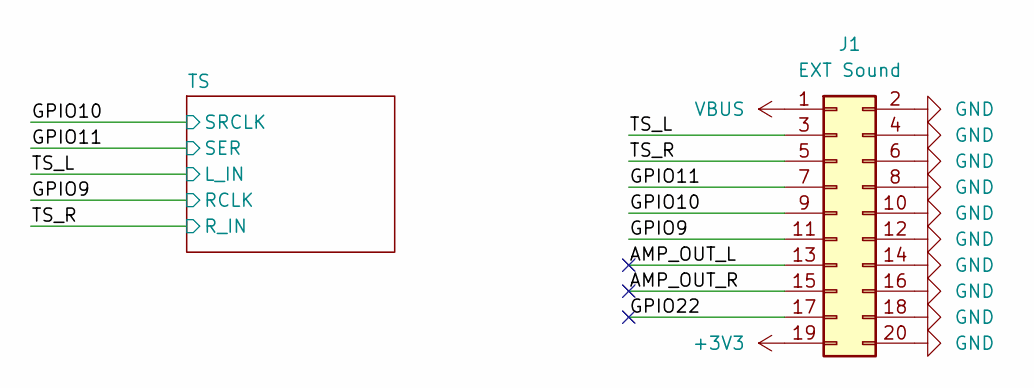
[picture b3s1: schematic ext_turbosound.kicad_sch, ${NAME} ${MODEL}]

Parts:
J1: EXT Sound; PinSocket_2x10_P2.54mm_Horizontal

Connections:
+3V3: J1.19
/AMP_OUT_L: J1.13
/AMP_OUT_R: J1.15
/GPIO9: J1.11; also elsewhere on the board
/GPIO10: J1.9; also elsewhere on the board
/GPIO11: J1.7; also elsewhere on the board
/GPIO22: J1.17
/TS_L: J1.3; also elsewhere on the board
/TS_R: J1.5; also elsewhere on the board
GND: J1.2, J1.4, J1.6, J1.8, J1.10, J1.12, J1.14, J1.16, J1.18, J1.20; also elsewhere on the board
VBUS: J1.1; also elsewhere on the board

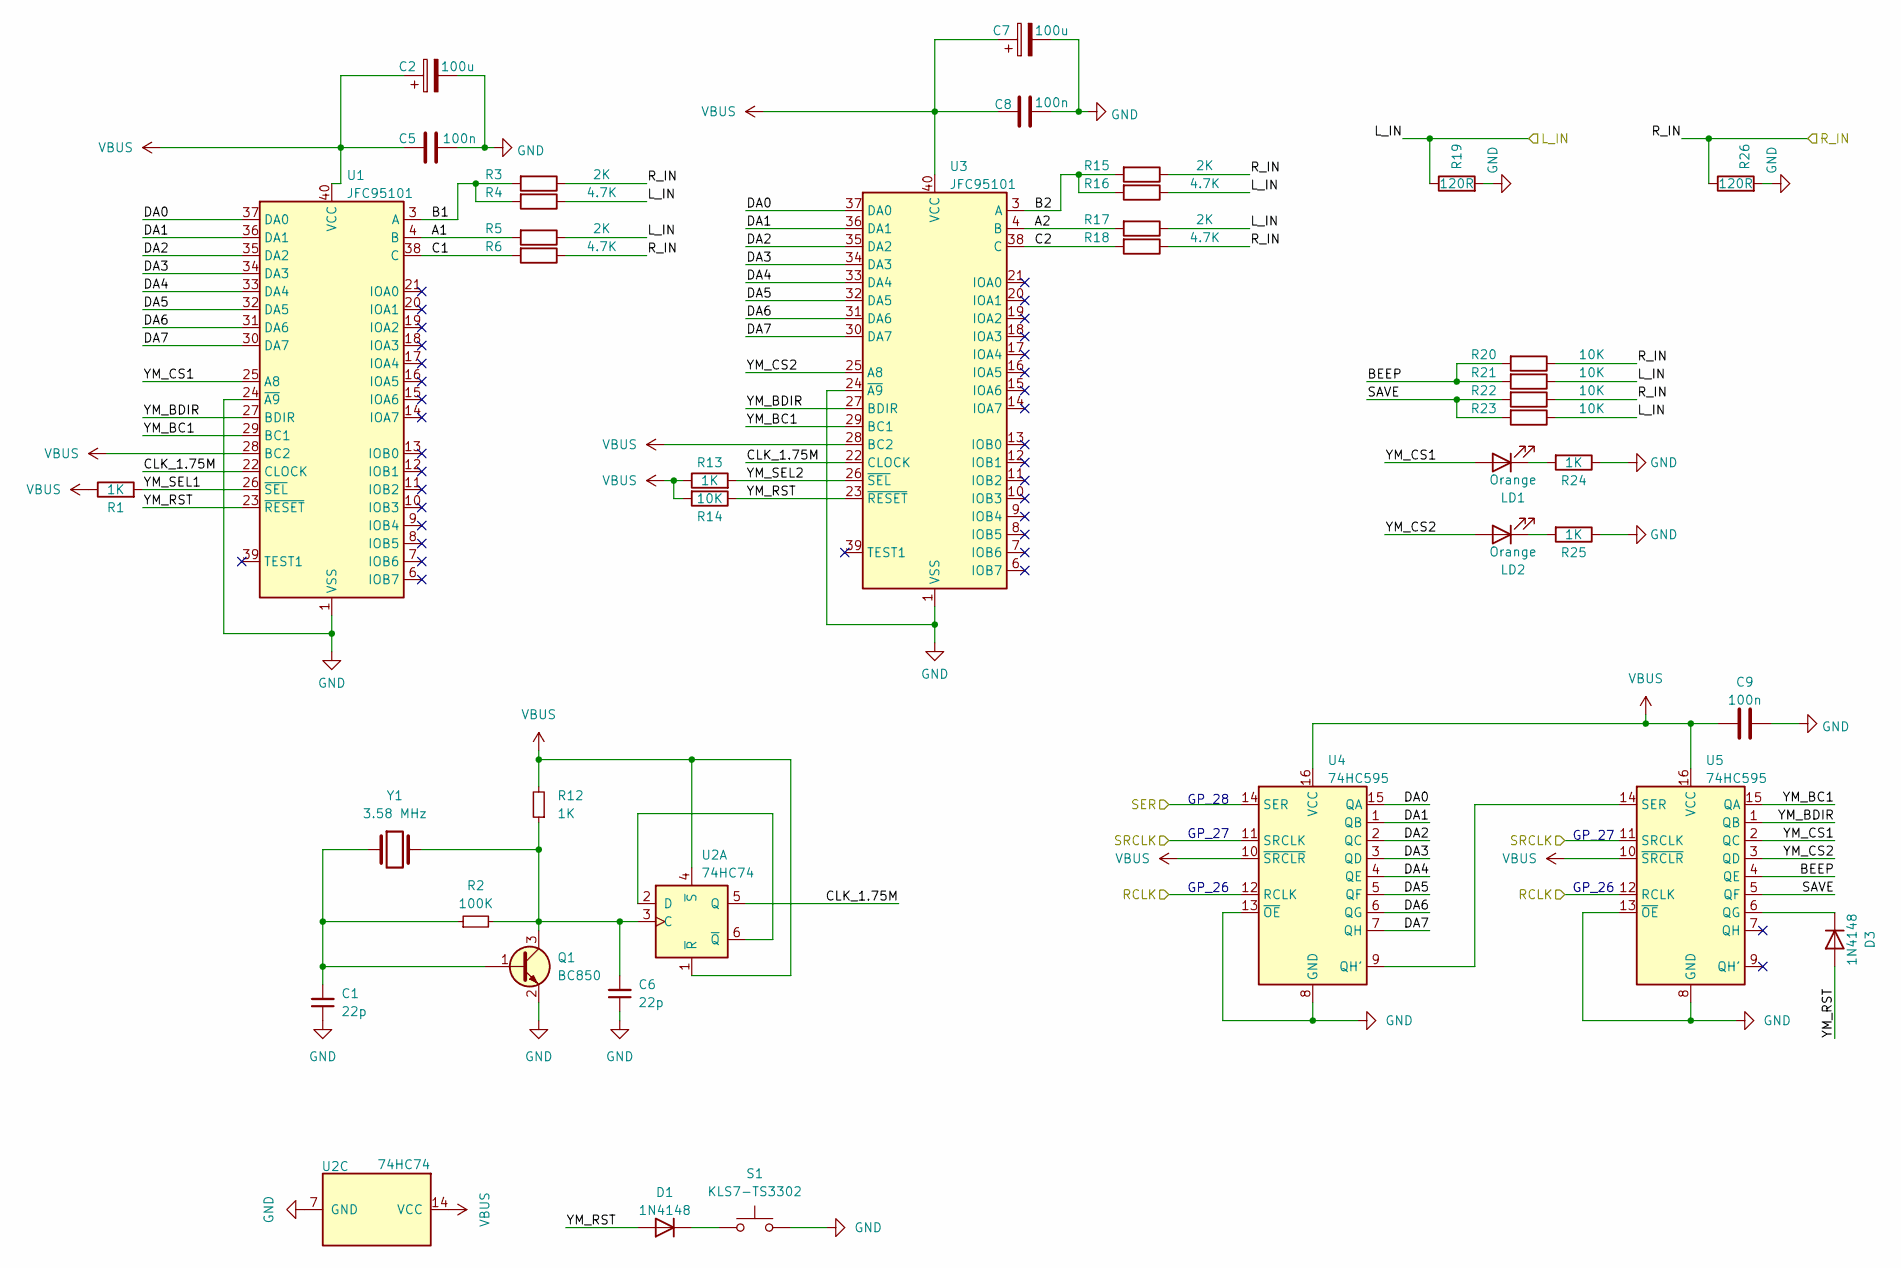
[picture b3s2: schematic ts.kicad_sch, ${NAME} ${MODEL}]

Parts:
C1, C6: 22p; Capacitor (0603, S)
C2, C7: 100u; Capacitor (3528, tantalum, polar)
C5, C8, C9: 100n; Capacitor (0603, S)
D1, D3: 1N4148; Diode (SOD-323)
LD1, LD2: Orange; LED (0805)
Q1: BC850; SOT-23
R1, R12, R13, R24, R25: 1K; Resistor (0603, S)
R2: 100K; Resistor (0603, S)
R3, R5, R15, R17: 2K; Resistor (0603, S)
R4, R6, R16, R18: 4.7K; Resistor (0603, S)
R14, R20, R21, R22, R23: 10K; Resistor (0603, S)
R19, R26: 120R; Resistor (0603, S)
S1: KLS7-TS3302; TACT-SIDE-4623
U1, U3: JFC95101; DIP-40 (Socket)
U2: 74HC74; 74HCT74D
U4, U5: 74HC595; SOP-16
Y1: 3.58 MHz; Crystal (HC49-S)

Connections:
/GPIO9: U4.12 (RCLK), U5.12 (RCLK); also elsewhere on the board
/GPIO10: U4.11 (SRCLK), U5.11 (SRCLK); also elsewhere on the board
/GPIO11: U4.14 (SER); also elsewhere on the board
/TS/A1: R5.2, U1.4 (B)
/TS/A2: R17.2, U3.4 (B)
/TS/B1: R3.2, R4.2, U1.3 (A)
/TS/B2: R15.2, R16.2, U3.3 (A)
/TS/BEEP: R20.2, R21.2, U5.4 (QE)
/TS/C1: R6.2, U1.38 (C)
/TS/C2: R18.2, U3.38 (C)
/TS/CLK_1.75M: U1.22 (CLOCK), U2.5 (Q), U3.22 (CLOCK)
/TS/DA0: U1.37 (DA0), U3.37 (DA0), U4.15 (QA)
/TS/DA1: U1.36 (DA1), U3.36 (DA1), U4.1 (QB)
/TS/DA2: U1.35 (DA2), U3.35 (DA2), U4.2 (QC)
/TS/DA3: U1.34 (DA3), U3.34 (DA3), U4.3 (QD)
/TS/DA4: U1.33 (DA4), U3.33 (DA4), U4.4 (QE)
/TS/DA5: U1.32 (DA5), U3.32 (DA5), U4.5 (QF)
/TS/DA6: U1.31 (DA6), U3.31 (DA6), U4.6 (QG)
/TS/DA7: U1.30 (DA7), U3.30 (DA7), U4.7 (QH)
/TS/SAVE: R22.2, R23.2, U5.5 (QF)
/TS/YM_BC1: U1.29 (BC1), U3.29 (BC1), U5.15 (QA)
/TS/YM_BDIR: U1.27 (BDIR), U3.27 (BDIR), U5.1 (QB)
/TS/YM_CS1: LD1.2 (A), U1.25 (A8), U5.2 (QC)
/TS/YM_CS2: LD2.2 (A), U3.25 (A8), U5.3 (QD)
/TS/YM_RST: D1.2 (A), D3.2 (A), R14.1, U1.23 (~RESET), U3.23 (~RESET)
/TS/YM_SEL1: R1.2, U1.26 (~SEL)
/TS/YM_SEL2: R13.2, U3.26 (~SEL)
/TS_L: R4.1, R5.1, R16.1, R17.1, R19.1, R21.1, R23.1; also elsewhere on the board
/TS_R: R3.1, R6.1, R15.1, R18.1, R20.1, R22.1, R26.1; also elsewhere on the board
GND: C1.1, C2.2, C5.2, C6.1, C7.2, C8.2, C9.2, Q1.2 (E), R19.2, R24.1, R25.1, R26.2, S1.2, U1.1 (VSS), U1.24 (~A9), U2.7 (GND), U3.1 (VSS), U3.24 (~A9), U4.8 (GND), U4.13 (~OE), U5.8 (GND), U5.13 (~OE); also elsewhere on the board
unnamed: D1.1 (K), S1.1
unnamed: D3.1 (K), U5.6 (QG)
unnamed: LD1.1 (K), R24.2
unnamed: LD2.1 (K), R25.2
unnamed: C1.2, Q1.1 (B), R2.1, Y1.1
unnamed: C6.2, Q1.3 (C), R2.2, R12.1, U2.3 (C), Y1.2
unnamed: U2.2 (D), U2.6 (~Q)
unnamed: U4.9 (QH'), U5.14 (SER)
VBUS: C2.1, C5.1, C7.1, C8.1, C9.1, R1.1, R12.2, R13.1, R14.2, U1.28 (BC2), U1.40 (VCC), U2.1 (~R), U2.4 (~S), U2.14 (VCC), U3.28 (BC2), U3.40 (VCC), U4.10 (~SRCLR), U4.16 (VCC), U5.10 (~SRCLR), U5.16 (VCC); also elsewhere on the board

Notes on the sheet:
GP_27
GP_26
GP_28
